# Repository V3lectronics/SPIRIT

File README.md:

Open source smartphone, from available components. Prioritizing user experience, performance, control, repairability, innovation and privacy.
Contribution and feedback are very welcome! **[Contribution Guide](https://github.com/V3lectronics/SPIRIT/blob/main/CONTRIBUTING.md)**.

We are currently in the development phase, progress is documented here and on the V Electronics **[YT channel](https://www.youtube.com/@V_Electronics)**. For information about the project please refer to the **[SPIRIT wiki](https://github.com/V3lectronics/SPIRIT/wiki)**.

> [!IMPORTANT]  
> Watch out for fake websites and repositories!
> 
> Before making suggestions and opening new discussions, search the **[issue list](https://github.com/V3lectronics/SPIRIT/issues)**!

# Quick links
1. **[Technical specifications](https://github.com/V3lectronics/SPIRIT/wiki/Overview-technical-specs)**
2. **[Hardware and electronics](https://github.com/V3lectronics/SPIRIT/wiki/Hardware-and-electronics)**
3. **[Software and operating System](https://github.com/V3lectronics/SPIRIT/wiki/Operating-system)**
4. **[SPIRIT wiki](https://github.com/V3lectronics/SPIRIT/wiki)**
5. **[Community](https://github.com/V3lectronics/SPIRIT/wiki/Community)**
6. **[Contribution guide](https://github.com/V3lectronics/SPIRIT/blob/main/CONTRIBUTING.md)**
7. **[Parts list](https://github.com/V3lectronics/SPIRIT/wiki/Parts-list)** _Coming soon!!!_
8. **[Cost](https://github.com/V3lectronics/SPIRIT/wiki/Cost)** _Coming soon!!!_
9. **[Ethical and environmental concerns](https://github.com/V3lectronics/SPIRIT/wiki/Ethical-and-environmental-concerns)**
10. **[Compliance and legality](https://github.com/V3lectronics/SPIRIT/wiki/Compliance-and-legality)**
11. **[DIY build guide](https://github.com/V3lectronics/SPIRIT/wiki/DIY-build-guide)** _Coming soon!!!_
12. **[Resources](https://github.com/barbarjan/SPIRIT#resources)**

# Roadmap

### **Chassis**  
[Public Onshape project](https://cad.onshape.com/documents/4e52c2512b67af09635f94b3/w/56ef775ef64c6c9cfce93a1f/e/4e6df7991d5269c6c76f6984) → Onshape 3D model *(in progress)* → 3D printable chassis → CNC chassis

### **Electronic systems**  
Select critical components → Footprints, symbols, 3D models → Power system *(in progress)* → Audio → GPS & GSM → LCD → Camera → Vibration & flashlight → Fingerprint scanner

### **Integration**
Integrate systems into one motherboard or modular setup.

### **OS**
Documented separately, see [OS article](https://github.com/V3lectronics/SPIRIT/wiki/Operating-system).

# Early screenshots
<small> (click to expand) </small>

<table>
  <tr>
    <td></td>
    <td></td>
    <td></td>
  </tr>
</table>

<table>
  <tr>
    <td></td>
    <td></td>
    <td></td>
  </tr>
</table>

# Resources
- [SPIRIT wiki](https://github.com/V3lectronics/SPIRIT/wiki)
- [Rpi CM5 datasheet](https://datasheets.raspberrypi.com/cm5/cm5-datasheet.pdf)
- [Rpi CM4 datasheet](https://datasheets.raspberrypi.com/cm4/cm4-datasheet.pdf)
- [Rpi CM5 and CM 4 useful interactive pinout](https://atctwo.net/projects/pinout/index.html)

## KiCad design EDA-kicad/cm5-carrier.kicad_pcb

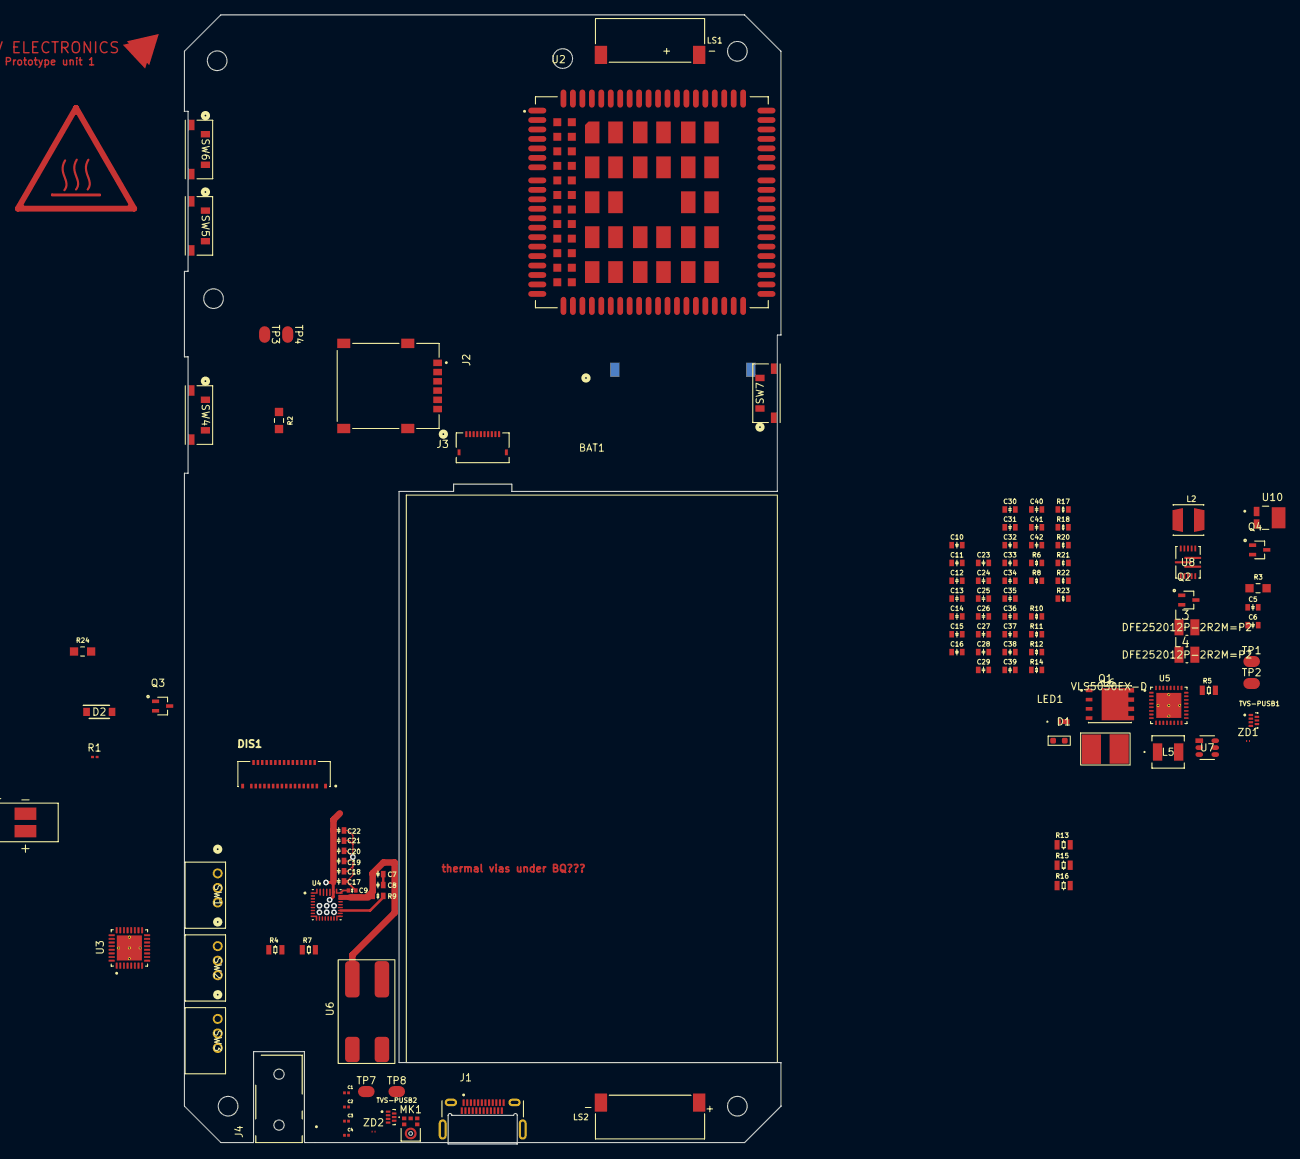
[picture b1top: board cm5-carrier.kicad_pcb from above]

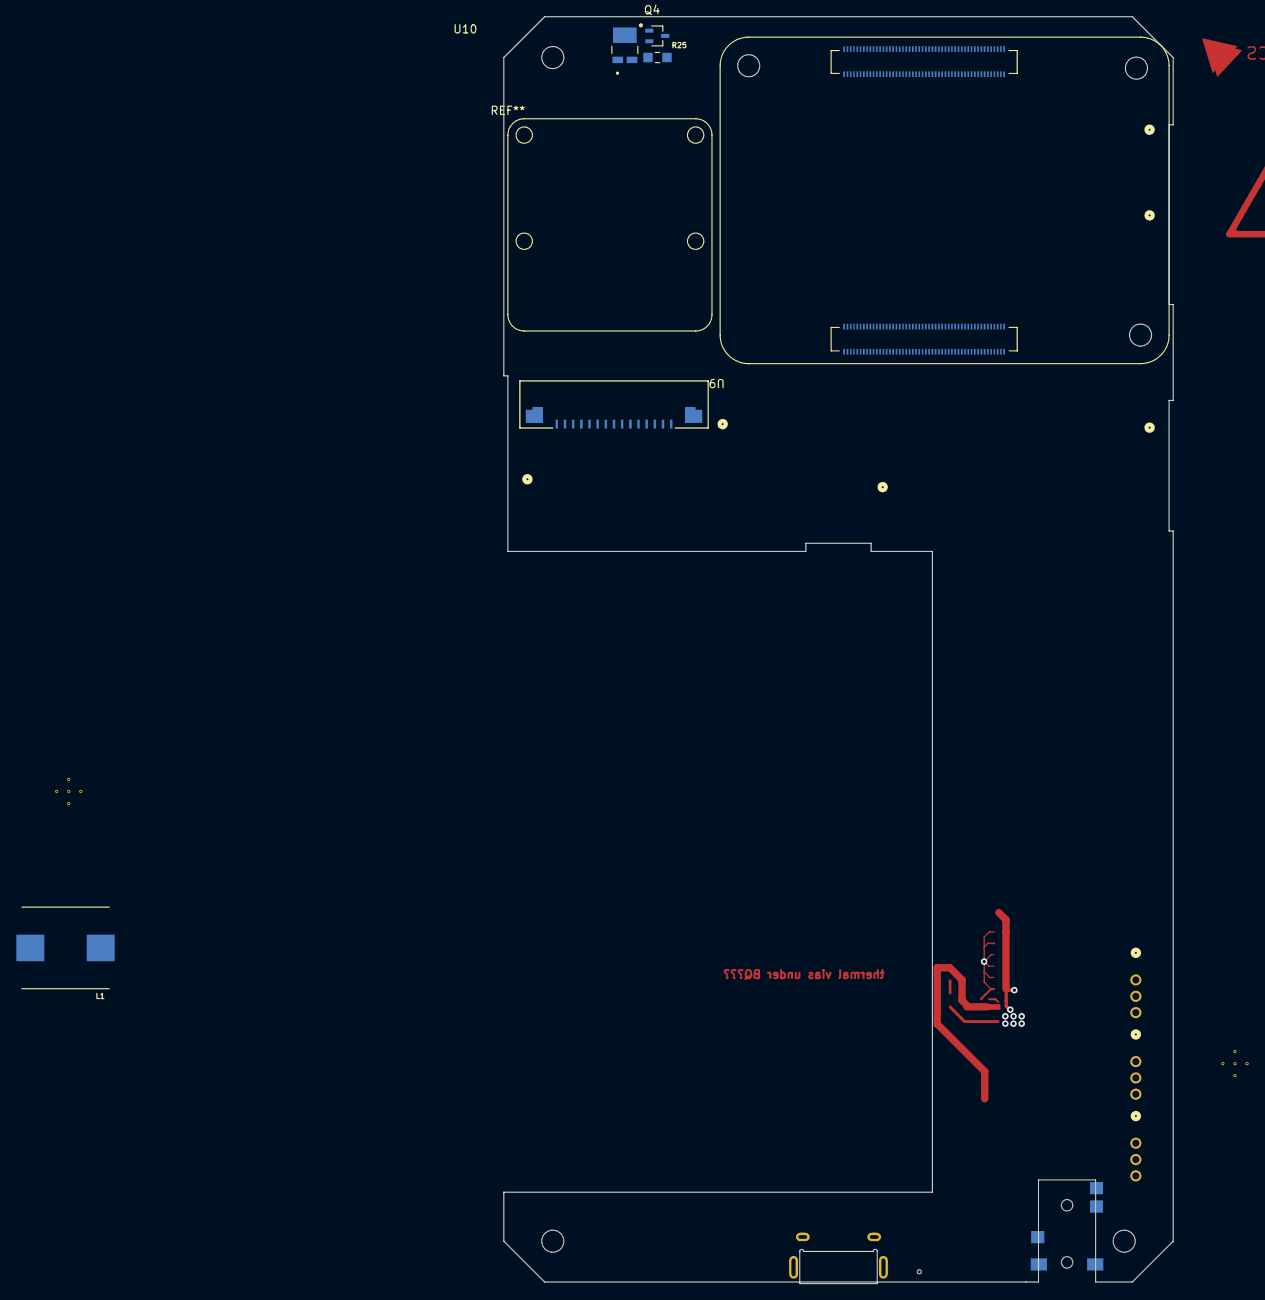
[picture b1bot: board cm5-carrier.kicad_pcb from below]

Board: 6 copper layers, 82.0 x 155.0 mm, 118 parts (6 on the bottom side), 94 nets.

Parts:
B1: VIBR; VIBRATION-PUI_HD-EMB1205-3-SC-R
BAT1: Li-ion-3.7 35Ah; battery_37V3500mAhLP685077JU
C1, C2, C3, C4: 0.33 µF coupling cap; USBC_capacitor_CAPC0603X33N
C5: 200-pf-CC0603KRX7R7BB104; 0603-capacitor
C6: 01-uf-CC0603KRX7R7BB104; 0603-capacitor
C7, C8, C12, C13, C14, C18, C19, C20, C21, C22, C24, C25, C26, C27, C28, C29: 10μF; 0603-capacitor
C9: 1nF 50V; 0402-capacitor
C10, C41: 4.7μF; 0603-capacitor
C11, C17, C32, C36: 0.1μF; 0603-capacitor
C15, C16: 47nF; 0603-capacitor
C23, C30, C31: 1μF; 0603-capacitor
C33, C34, C35, C37, C38, C39, C42: 22μF; 0603-capacitor
C40: 6.8nF; 0603-capacitor
D1: D_Schottky; schottky-diode-CR_DSN2_152AB-C_OSI
D2: 1N4007W-T; flyback-diode-SODFL3818X130N
DIS1: FH72-31S-0.3SHW; HRS_FH72-31S-0.3SHW
J1: USBC-4-0-CX90MW9-24P1; USB-4-0-HIROSE_CX90MW9-24P1
J2: SIM-G85D1160022HHR; SIM-AMPHENOL_G85D1160022HHR
J3: FINGER; 10PIN
J4: SJ2-35894B-SMT-TR; 35mmJACK-CUI_SJ2-35894B-SMT-TR
L1: 2.2uH; 2-2uh-inductorIND_ETQP4M2R2KVC
L2: 3.3uH; 3-3uH-MURATA_LQH44PN3R3MPRL
L3, L4: 2.2uH; 2-2uH-inductor-INDC2520X120N
L5: 6.8uH; 6-8uH-inductor-LQH44PN6R8MPRLIND_LQH44PN_PR_MUR
L6: 1.5uH; 1-5uH-inductor-VLS5030EX-D
LED1: 5mA 2V Fv; LED-INDICATOR-RED-QBLP601-R5
LS1, LS2: CMR-15062S-67; SPEAKER_CMR-15062S-67
MK1: microphone; microphone_SPH0645LM4H-B
Module1: ComputeModule5-CM5; Raspberry-Pi-5-Compute-Module
Q1: NMOS-BSC0902NSIATMA1-PG-TDSON-8-6-IC_ISC037N03L5ISATMA1
Q2, Q3, Q4, Q4#2: gpio-driver-transistor-fix-SOT65P210X110-3N
R1: thermistor; thermistor-NTC0201Z_P63XP33_PAN
R2: 270K-05W-0805-RES_ERJP06J102V; 1K-05W-0805-RES_ERJP06J102V
R3: 100K-0805-resistor-ERA6AEB104V; 100K-0805-resistor-RES_ERA6AEB104V
R4: 127k; 0805-resistor
R5: 4.7K; 0805-resistor
R6: 820k; 0603-resistor
R7: 100k; 0805-resistor
R8: 47k; 0603-resistor
R9: 100; 0603-resistor
R10: 182K; 0603-resistor
R11: 1M; 0603-resistor
R12: 470k; 0603-resistor
R13: 5.23k; 0805-resistor
R14, R18: 10k; 0603-resistor
R15: 10k; 0805-resistor
R16: 30k; 0805-resistor
R17: 680; 0603-resistor
R20: 5; 0603-resistor
R21: 750k; 0603-resistor
R22: 200k; 0603-resistor
R23: 6.8k; 0603-resistor
R24: 1K-05W-0805-RES_ERJP06J102V
R25: 1K; 1K-05W-0805-RES_ERJP06J102V
SW1: EG25-switch-CSS-1210MC; privacy-switch-SW3_CSS-1210MC_NDC
SW2: MIC-switch-CSS-1210MC; privacy-switch-SW3_CSS-1210MC_NDC
SW3: CAM-switch-CSS-1210MC; privacy-switch-SW3_CSS-1210MC_NDC
SW4: PROG; buttonSW_TL3330_EWI
SW5: VOL-; buttonSW_TL3330_EWI
SW6: VOL+; buttonSW_TL3330_EWI
SW7: POW; buttonSW_TL3330_EWI
TP1, TP2, TP3, TP4, TP7, TP8: test-pad-1
TVS-PUSB1, TVS-PUSB2: TVS-array-IC_PUSB3AB6Z
U2: EG25GGC-128-SGNS; XCVR_EG25GGC-128-SGNS
U3: CODEC-TLV320AIC3204IRHBR; CODEC-QFN50P500X500X100-33N
U4: BQ25792RQMR; charger-bq25792-QFN40P400X400X100-29N
U5: TPS650250RHBR; TPS650250-IC_ADS125H01IRHBT
U6: BAT-CONNECTOR-FLTS22WR00
U7: 22V-boost-AP3032KTR-G1; SOT23-6_DIO
U8: MP3429GL-Z; QFN-3x4_MP3429_MNP
U9: FPC15pin-1mm-pitch-F52Q-1A7H1-11015; FPC15pin-1mm-pitch-CONN_F52Q-1A7H1-11015_AMP
U10, U10#2: Flash-LED-Lumiled; LUMILED-DIODFN449X305X210-3N
ZD1, ZD2: protection-PESD5V0C1USFYL; USB-ESD-protection-diode-PESD5V0C1USFYL-SOD962-2_DSN0603-2_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

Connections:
1V8: C28.1, DIS1.25, L3.1, U5.25 (VDCDC2)
3V3A: C27.1, L2.1, U5.8 (VDCDC1)
3V3B: C29.1, DIS1.30, L4.1, Q2.3 (S), R6.1, SW2.1, SW3.1, U5.1 (VDCDC3)
5V: C36.1, C37.1, C38.1, C39.1, R21.1, U8.8 (VOUT)
22V: C30.1, D1.1 (K), DIS1.2, U7.5 (OV)
AGND: C42.2, R22.2, R23.2, U5.13 (AGND2), U5.17 (EN_LDO), U5.22 (DEFDCDC2), U5.23 (MODE), U5.24 (EN_VDD_ALIVE), U5.31 (AGND1), U5.33 (EP), U8.6 (AGND), U8.9 (FTY)
AUDIO_BCLK_I2S: MK1.4 (BCLK), Module1.49 (GPIO18), U3.2 (BCLK)
AUDIO_MCLK: Module1.41 (GPIO25), U3.1 (MCLK)
AUDIO_MIC_DATA: MK1.6 (DATA_OUT), Module1.27 (GPIO20), R3.2
AUDIO_SCL: Module1.51 (GPIO15), U3.9 (SCL/~SS)
AUDIO_SDA: Module1.31 (GPIO12), U3.10 (SDA/MOSI)
AUDIO_WCLK_I2S: MK1.1 (WS), Module1.26 (GPIO19), U3.3 (WCLK)
BACKLIGHT-: C5.1, C6.2, C7.2, C8.2, C9.2, C10.2, C11.2, C12.2, C13.2, C14.2, C17.2, C18.2, C19.2, C20.2, C21.2, C22.2, C23.2, C24.2, C25.2, C26.2, C27.2, C28.2, C29.2, C30.2, C31.2, C33.2, C34.2, C35.2, C36.2, C37.2, C38.2, C39.2, C41.1, DIS1.1, DIS1.4, DIS1.7, DIS1.10, DIS1.13, DIS1.16, DIS1.19, DIS1.20, DIS1.31, J1.A1 (GND_A), J1.A12 (GND_A__1), J1.B1 (GND_B), J1.B12 (GND_B__1), J1.SH1 (SHIELD), J1.SH2 (SHIELD__1), J1.SH3 (SHIELD__2), J1.SH4 (SHIELD__3), J2.C5 (GND), J2.S1 (SHIELD_GND), J2.S2 (SHIELD_GND__1), J2.S3 (SHIELD_GND__2), J3.1, MK1.2 (SELECT), MK1.3 (GND), Module1.1 (GND), Module1.2 (GND), Module1.8 (GND), Module1.13 (GND), Module1.14 (GND), Module1.22 (GND), Module1.23 (GND), Module1.32 (GND), Module1.33 (GND), Module1.42 (GND), Module1.43 (GND), Module1.52 (GND), Module1.53 (GND), Module1.60 (GND), Module1.66 (GND), Module1.71 (GND), Module1.74 (GND), Module1.98 (GND), Module1.107 (GND), Module1.108 (GND), Module1.113 (GND), Module1.114 (GND), Module1.119 (GND), Module1.120 (GND), Module1.125 (GND), Module1.126 (GND), Module1.131 (GND), Module1.132 (GND), Module1.137 (GND), Module1.138 (GND), Module1.144 (GND), Module1.150 (GND), Module1.155 (GND), Module1.156 (GND), Module1.161 (GND), Module1.162 (GND), Module1.167 (GND), Module1.168 (GND), Module1.173 (GND), Module1.174 (GND), Module1.179 (GND), Module1.180 (GND), Module1.185 (GND), Module1.186 (GND), Module1.191 (GND), Module1.192 (GND), Module1.197 (GND), Module1.198 (GND), Q3.3 (S), Q4.3 (S), Q4#2.3 (S), R3.1, R5.1, R7.2, R10.1, R12.1, R15.2, R16.2, R20.1, R20.2, TVS-PUSB1.2 (GND), U3.7 (IOVSS), U3.17 (AVSS), U3.28 (DVSS), U4.10 (ACDRV2), U4.11 (ACDRV1), U4.27 (GND), U5.2 (PGND3), U5.7 (PGND1), U5.26 (PGND2), U6.4 (OUT-), U7.2 (GND), U7.3 (FB), U8.7 (PGND), U9.1, U9.4, U9.10, ZD1.2
BAT+: C7.1, C8.1, R9.2, U4.22 (BAT), U4.23 (BAT__1), U6.3 (OUT+)
CAM-SWITCH: TP3.1 (A), U9.15
CAM_CK_N: Module1.127 (MIPI0_C_N), U9.8
CAM_CK_P: Module1.129 (MIPI0_C_P), U9.9
CAM_D0_N: Module1.115 (MIPI0_D0_N), U9.2
CAM_D0_P: Module1.117 (MIPI0_D0_P), U9.3
CAM_D1_N: Module1.121 (MIPI0_D1_N), U9.5
CAM_D1_P: Module1.123 (MIPI0_D1_P), U9.6
CAM_IO0: TP4.1 (A), U9.11
CC1: J1.A5 (CC1), Module1.94 (CC1)
CC2: J1.B5 (CC2), Module1.96 (CC2)
D+: J1.A6 (D1+), J1.B6 (D2+), Module1.163 (USB3-1-D_P), TVS-PUSB1.5 (D+), TVS-PUSB2.5 (D+), U4.6 (D+)
D-: J1.A7 (D1-), J1.B7 (D2-), Module1.165 (USB3-1-D_N), TVS-PUSB1.4 (D-), TVS-PUSB2.4 (D-), U4.7 (D-)
DSI1_C_N: DIS1.11, Module1.187 (MIPI1_C_N)
DSI1_C_P: DIS1.12, Module1.189 (MIPI1_C_P)
DSI1_D0_N: DIS1.5, Module1.175 (MIPI1_D0_N)
DSI1_D0_P: DIS1.6, Module1.177 (MIPI1_D0_P)
DSI1_D1_N: DIS1.8, Module1.181 (MIPI1_D1_N)
DSI1_D1_P: DIS1.9, Module1.183 (MIPI1_D1_P)
DSI1_D2_N: DIS1.14, Module1.133 (MIPI0_D2_N), Module1.193 (MIPI1_D2_N)
DSI1_D2_P: DIS1.15, Module1.135 (MIPI0_D2_P), Module1.195 (MIPI1_D2_P)
EN3V3A-SW-OUT: SW1.2, U5.20 (EN_DCDC1)
GND: TVS-PUSB2.2 (GND), ZD2.2
GPIO2: Module1.58 (GPIO2), SW7.2
GPIO3: Module1.56 (GPIO3), SW6.2
GPIO4: Module1.54 (GPIO4), SW5.2
GPIO17: Module1.50 (GPIO17), SW4.2
GPIO22: Module1.46 (GPIO22), R25.1
GPIO27: Module1.48 (GPIO27), R24.1
LCD_PWM: Module1.55 (GPIO14), U7.4 (CTRL)
MIC-SWITCH: C5.2, C6.1, MK1.5 (VDD)
unnamed: C40.2, R23.1
unnamed: D1.2 (A), L5.2, U7.1 (SW)
unnamed: J3.8, R2.2
unnamed: LED1.2 (A), R17.1
unnamed: LED1.1 (K), R14.1, U4.1 (STAT)
unnamed: C1.1, Module1.157 (USB3-1-RX_N)
unnamed: C2.1, Module1.159 (USB3-1-RX_P)
unnamed: C3.1, Module1.169 (USB3-1-TX_N)
unnamed: C4.1, Module1.171 (USB3-1-TX_P)
unnamed: Q2.1 (G), SW3.2
unnamed: B1.N, D2.2, Q3.2 (D)
unnamed: Q3.1 (G), R24.2
unnamed: Q4.2 (D), Q4#2.2 (D), U10.1 (-), U10#2.1 (-)
unnamed: Q4.1 (G), Q4#2.1 (G), R25.2
unnamed: R9.1, U4.18 (BATP)
unnamed: C15.2, U4.4 (BTST1)
unnamed: C16.2, U4.19 (BTST2)
unnamed: R4.1, R7.1, U4.17 (ILIM_HIZ)
unnamed: C11.1, C12.1, C13.1, C14.1, U4.29 (PMID)
unnamed: R5.2, U4.20 (PROG)
unnamed: C9.1, U4.24 (SDRV)
unnamed: C15.1, L1.2, U4.28 (SW1)
unnamed: C16.1, L1.1, U4.26 (SW2)
unnamed: R13.2, R15.1, R16.1, U4.16 (TS)
unnamed: R6.2, R10.2, U5.32 (DEFDCDC3)
unnamed: L2.2, U5.6 (L1)
unnamed: L3.2, U5.27 (L2)
unnamed: L4.2, U5.3 (L3)
unnamed: R11.1, R12.2, U5.30 (PWRFAIL_SNS)
unnamed: C32.1, U8.13 (BST)
unnamed: C40.1, U8.4 (COMP)
unnamed: R21.2, R22.1, U8.5 (FB)
unnamed: C42.1, U8.3 (SS)
unnamed: C32.2, L6.2, U8.1 (SW)
unnamed: C41.2, U8.2 (VDD)
REGN: C10.1, R4.2, R13.1, R17.2, U4.5 (REGN)
RX1+: C2.2, J1.A11 (RX2+), J1.B11 (RX1+), TVS-PUSB1.7 (RX+), TVS-PUSB2.7 (RX+)
RX1-: C1.2, J1.A10 (RX2-), J1.B10 (RX1-), TVS-PUSB1.6 (Rx-), TVS-PUSB2.6 (Rx-)
SPI0_CLK: J3.2, Module1.38 (GPIO11)
SPI0_CS: J3.5, Module1.39 (GPIO8)
SPI0_MISO: J3.3, Module1.40 (GPIO9)
SPI0_MOSI: J3.4, Module1.44 (GPIO10)
SPI0_RDY: J3.6, Module1.34 (GPIO5)
SYS: C17.1, C18.1, C19.1, C20.1, C21.1, C22.1, C23.1, C24.1, C25.1, C26.1, C31.1, C33.1, C34.1, C35.1, L5.1, L6.1, R11.2, U4.25 (SYS), U5.4 (VINDCDC3), U5.5 (VINDCDC1), U5.9 (DEFDCDC1), U5.28 (VINDCDC2), U5.29 (VCC), U7.6 (VIN), U8.10 (MODE), U8.11 (EN), U8.12 (VIN)
TX1+: C4.2, J1.A2 (TX1+), J1.B2 (TX2+), TVS-PUSB1.3 (Tx+), TVS-PUSB2.3 (Tx+)
TX1-: C3.2, J1.A3 (TX1-), J1.B3 (TX2-), TVS-PUSB1.1 (Tx-), TVS-PUSB2.1 (Tx-)
USBC POW: J1.A4 (VBUS_A), J1.A9 (VBUS_A__1), J1.B4 (VBUS_B), J1.B9 (VBUS_B__1), U4.2 (VBUS), U4.8 (VAC2), U4.9 (VAC1), ZD1.1, ZD2.1
VCC: B1.P, D2.1, J3.7, J3.10, R2.1, R14.2, R18.1, SW4.1, SW5.1, SW6.1, SW7.1, U3.24 (AVDD), U10.2 (+), U10#2.2 (+)
~INT: R18.2, U4.21 (~INT)
~PWRFAIL: R8.2, U5.21 (~PWRFAIL)
